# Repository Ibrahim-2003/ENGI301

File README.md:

# ENGI301
Engineering Design: Intro to Practical Electrical Engineering

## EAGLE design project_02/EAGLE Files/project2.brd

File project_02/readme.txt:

Github Link: https://github.com/Ibrahim-2003/ENGI301
--------------------------------------
Library Components:
POCKETBEAGLE (device and footprint)
POCKETBEAGLE_PWR (symbol)
POCKETBEAGLE_SIGNALS (symbol)
POCKETBEAGLE_MISC (symbol)
SPI_SCREEN (device, footprint, and symbol)
*** All other library components were imported from combo_lock.lbr ***
--------------------------------------
MicroFab Login:
USERNAME: isa1@rice.edu
PASSWORD: deeznuts
*** Note: Please excuse the silly password name, I had already created the account prior to knowing we were supposed to turn it in ***
--------------------------------------
Price Quotes:
*** Detailed in "MicroFab Price Quotes.csv" ***

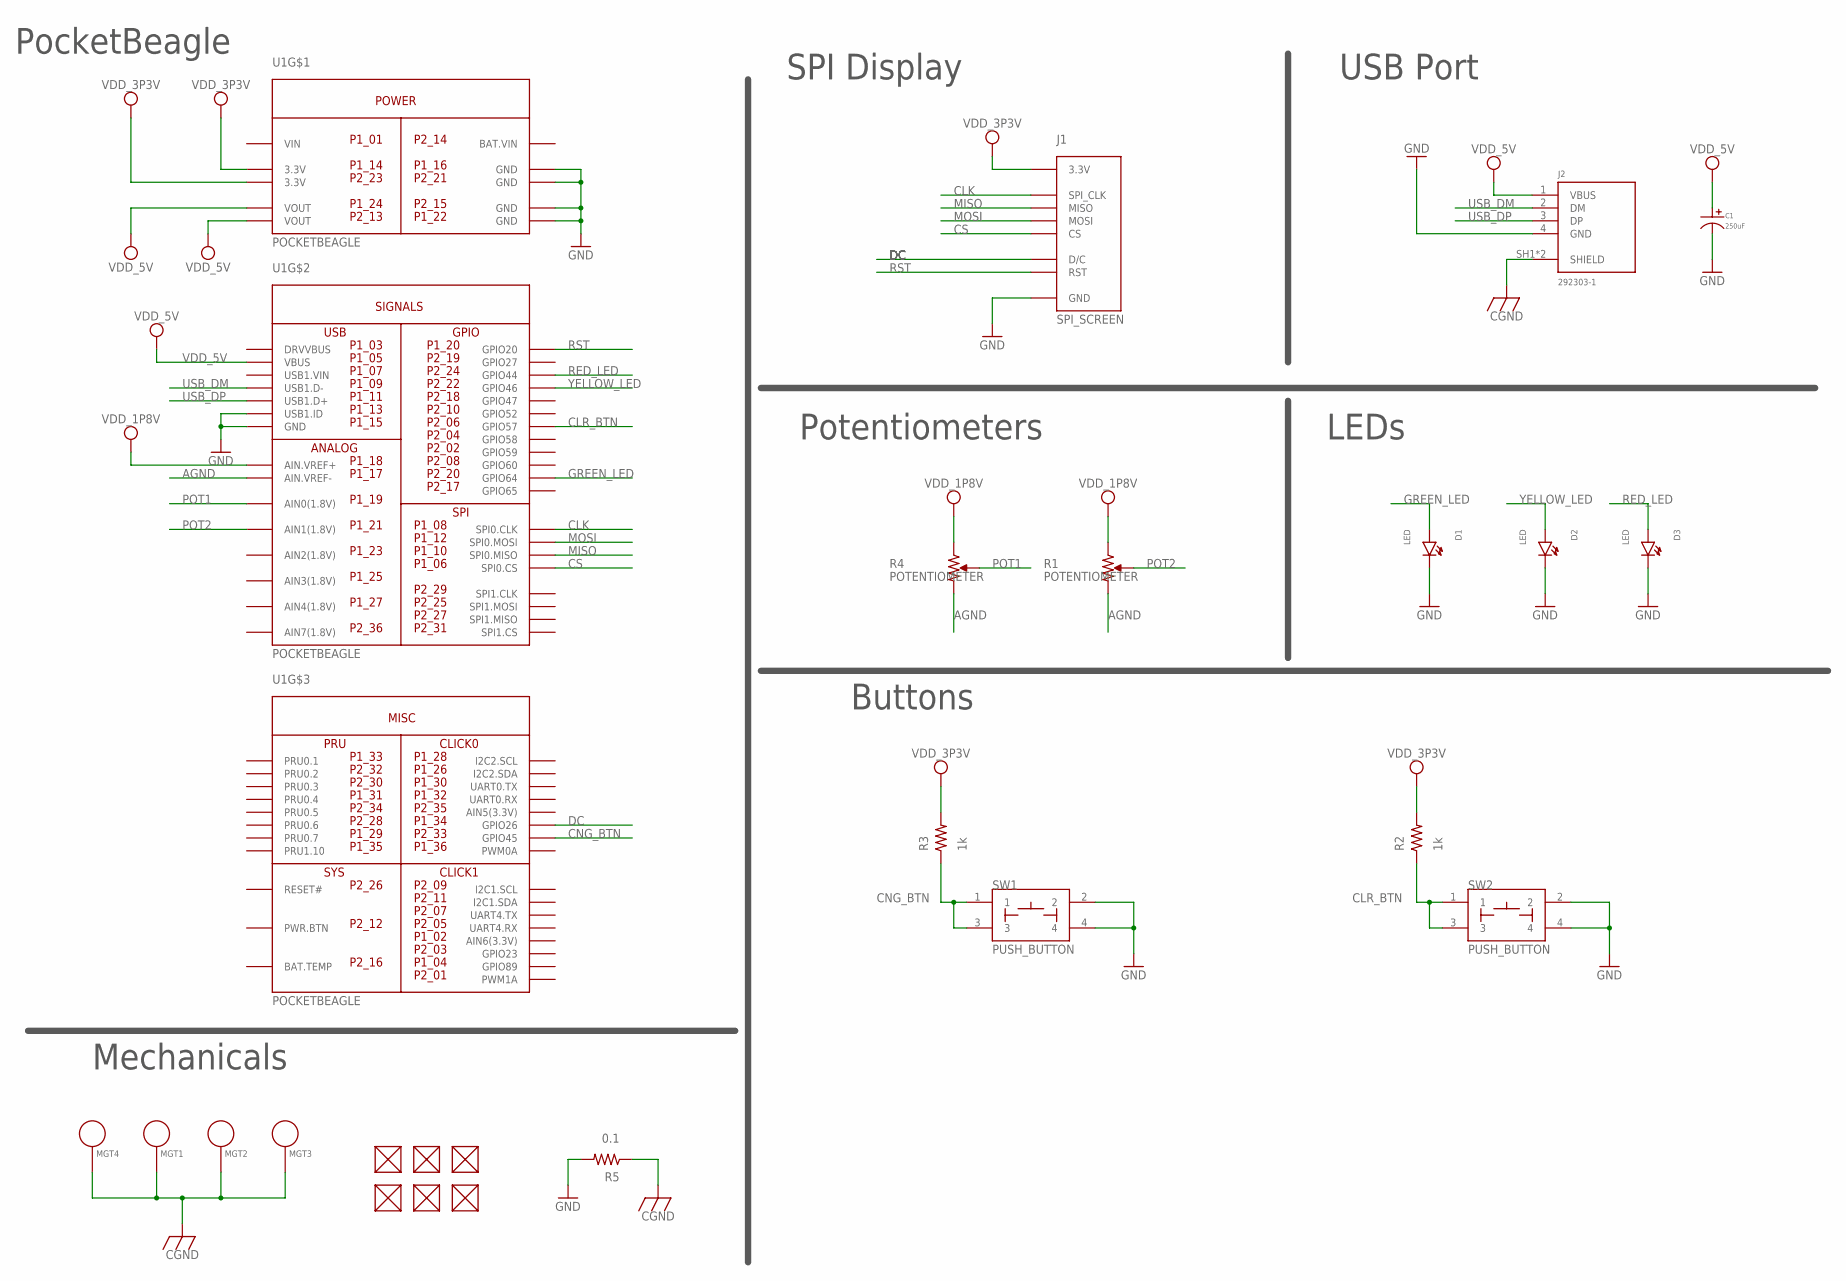
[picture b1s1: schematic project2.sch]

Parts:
C1: 250uF; CP10MM
D1, D2, D3: LED; EIA-STD
FUD1, FUD2, FUD3, FUD4, FUD5, FUD6: FIDUCIAL; FIDUCIAL_40MIL
J1: SPI_SCREEN
J2: 292303-1; TE_292303-1
MGT1, MGT2, MGT3, MGT4: MOUNTING_HOLE
R1, R4: POTENTIOMETER; POT-PO90S
R2, R3: 1k; R0603
R5: 0.1; R0603
SW1, SW2: PUSH_BUTTON; BUTTON_12.5MM
U1: POCKETBEAGLE

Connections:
AGND: R1.CW, R4.CW, U1.17@P1 (AIN.VREF-)
BAT.VIN: U1.14@P2 (BAT.VIN)
CGND: J2.SH1 (SHIELD), J2.SH2 (SHIELD), MGT1.P$1, MGT2.P$1, MGT3.P$1, MGT4.P$1, R5.1
CLK: J1.4@JP2 (SPI_CLK), U1.8@P1 (SPI0.CLK)
CLR_BTN: R2.1, SW2.1, SW2.3, U1.6@P2 (GPIO57)
CNG_BTN: R3.1, SW1.1, SW1.3, U1.33@P2 (GPIO45)
CS: J1.7@JP2 (CS), U1.6@P1 (SPI0.CS)
DC: J1.8@JP2 (D/C), U1.34@P1 (GPIO26)
GND: C1.P$2, D1.CATHODE, D2.CATHODE, D3.CATHODE, J1.1@JP2 (GND), J2.4 (GND), R5.2, SW1.2, SW1.4, SW2.2, SW2.4, U1.13@P1 (USB1.ID), U1.15@P1 (GND), U1.15@P2 (GND), U1.16@P1 (GND), U1.21@P2 (GND), U1.22@P1 (GND)
GREEN_LED: D1.ANODE, U1.20@P2 (GPIO64)
MISO: J1.5@JP2 (MISO), U1.10@P1 (SPI0.MISO)
MOSI: J1.6@JP2 (MOSI), U1.12@P1 (SPI0.MOSI)
POT1: R4.S, U1.19@P1 (AIN0(1.8V))
POT2: R1.S, U1.21@P1 (AIN1(1.8V))
RED_LED: D3.ANODE, U1.24@P2 (GPIO44)
RST: J1.9@JP2 (RST), U1.20@P1 (GPIO20)
USB_DM: J2.2 (DM), U1.9@P1 (USB1.D-)
USB_DP: J2.3 (DP), U1.11@P1 (USB1.D+)
VDD_1P8V: R1.CCW, R4.CCW, U1.18@P1 (AIN.VREF+)
VDD_3P3V: J1.3@JP2 (3.3V), R2.2, R3.2, U1.14@P1 (3.3V), U1.23@P2 (3.3V)
VDD_5V: C1.P$1, J2.1 (VBUS), U1.5@P1 (VBUS), U1.13@P2 (VOUT), U1.24@P1 (VOUT)
VIN: U1.1@P1 (VIN)
YELLOW_LED: D2.ANODE, U1.22@P2 (GPIO46)

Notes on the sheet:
PocketBeagle
SPI Display
USB Port
Potentiometers
LEDs
Buttons
Mechanicals

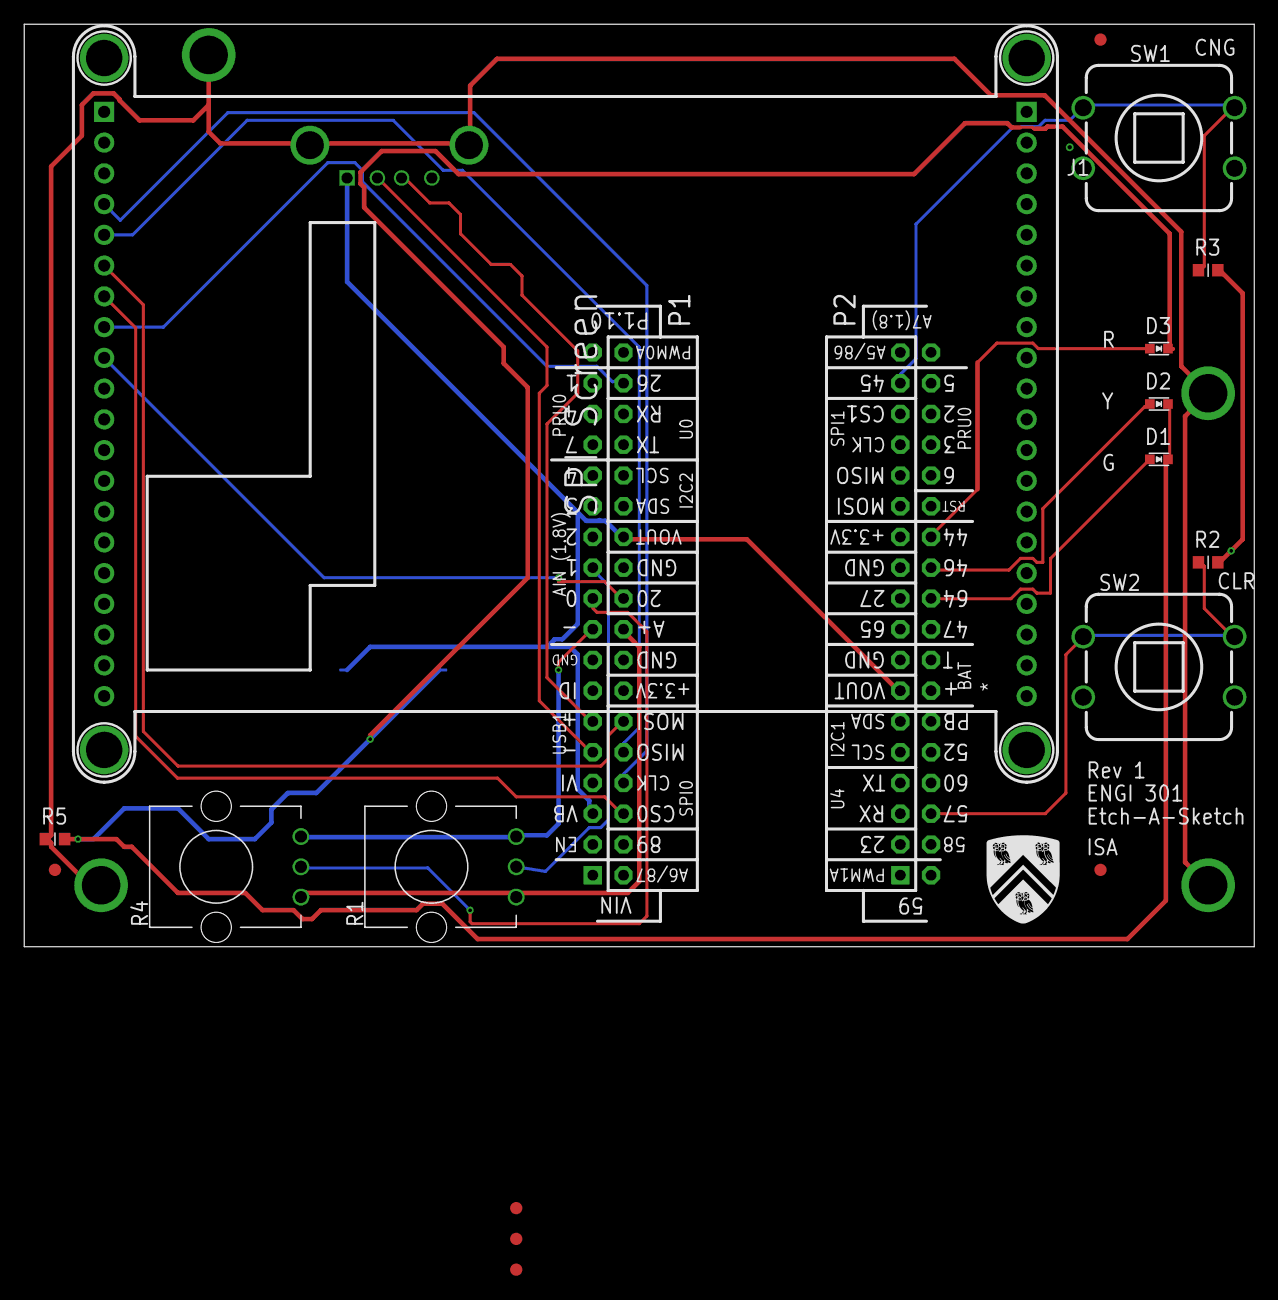
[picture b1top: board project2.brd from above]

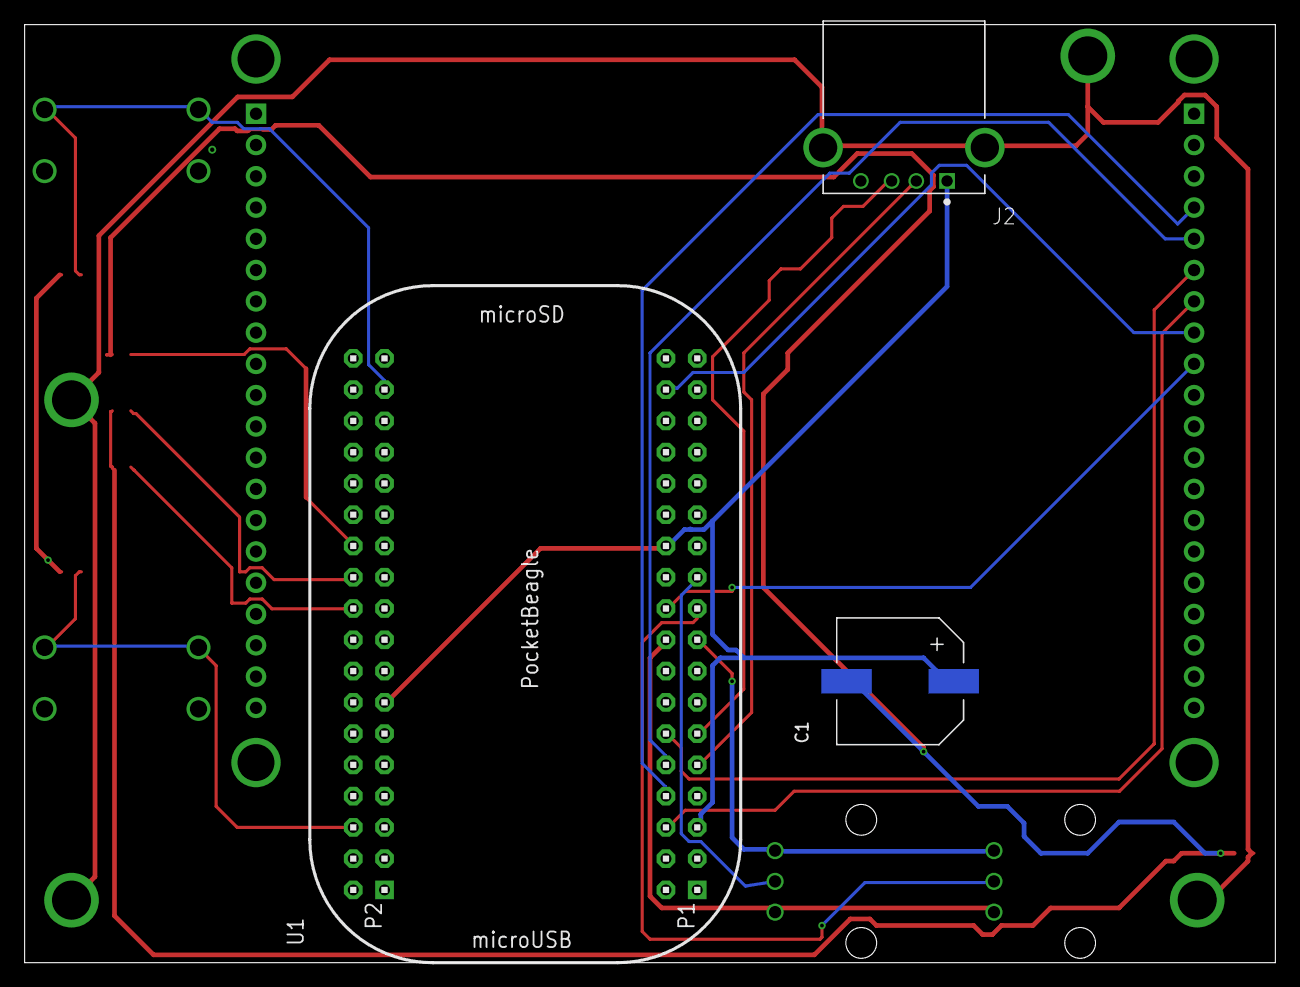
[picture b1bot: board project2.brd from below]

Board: 4 copper layers, 101.6 x 76.2 mm, 24 parts (3 on the bottom side), 21 nets.

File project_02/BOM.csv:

Designator,Value,Footprint,Populate,MPN,Manufacturer
C1,250uF,CP10MM,1,MF-CAP-10MM-220uF,MacroFab
D1,LED,EIA-STD,1,MF-LED-0603-GREEN,MacroFab
D2,LED,EIA-STD,1,MF-LED-0603-GREEN,MacroFab
D3,LED,EIA-STD,1,MF-LED-0603-GREEN,MacroFab
FUD1,FIDUCIAL,FIDUCIAL_40MIL,0,5-1567064-5,TE Connectivity / AMP
FUD2,FIDUCIAL,FIDUCIAL_40MIL,0,5-1567064-5,TE Connectivity / AMP
FUD3,FIDUCIAL,FIDUCIAL_40MIL,0,5-1567064-5,TE Connectivity / AMP
FUD4,FIDUCIAL,FIDUCIAL_40MIL,0,5-1567064-5,TE Connectivity / AMP
FUD5,FIDUCIAL,FIDUCIAL_40MIL,0,5-1567064-5,TE Connectivity / AMP
FUD6,FIDUCIAL,FIDUCIAL_40MIL,0,5-1567064-5,TE Connectivity / AMP
J1,SPI_SCREEN,SPI_SCREEN,1,1770,Adafruit Industries
J2,292303-1,TE_292303-1,1,292303-1,TE Connectivity
MGT1,MOUNTING_HOLE,MOUNTING_HOLE,0,2516672_WO_CORNER_MOUNTING_HOLES,Texas Instruments
MGT2,MOUNTING_HOLE,MOUNTING_HOLE,0,2516672_WO_CORNER_MOUNTING_HOLES,Texas Instruments
MGT3,MOUNTING_HOLE,MOUNTING_HOLE,0,2516672_WO_CORNER_MOUNTING_HOLES,Texas Instruments
MGT4,MOUNTING_HOLE,MOUNTING_HOLE,0,2516672_WO_CORNER_MOUNTING_HOLES,Texas Instruments
R1,POTENTIOMETER,POT-PO90S,1,MF-RES-TC33X-10K,MacroFab
R2,1k,R0603,1,MF-RES-0603-1K,MacroFab
R3,1k,R0603,1,MF-RES-0603-1K,MacroFab
R4,POTENTIOMETER,POT-PO90S,1,MF-RES-TC33X-10K,MacroFab
R5,0.1,R0603,1,ERJ-L03KF10CV,Panasonic
SW1,PUSH_BUTTON,BUTTON_12.5MM,1,TINKERKIT PUSHBUTTON,Arduino
SW2,PUSH_BUTTON,BUTTON_12.5MM,1,TINKERKIT PUSHBUTTON,Arduino
U1,POCKETBEAGLE,POCKETBEAGLE,1,POCKETBEAGLE,BeagleBoard

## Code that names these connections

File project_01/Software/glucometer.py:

# -*- coding: utf-8 -*-
"""
--------------------------------------------------------------------------
Glucometer Code
--------------------------------------------------------------------------
License:   
Copyright 2022 Ibrahim Al-Akash

Redistribution and use in source and binary forms, with or without 
modification, are permitted provided that the following conditions are met:

1. Redistributions of source code must retain the above copyright notice, this 
list of conditions and the following disclaimer.

2. Redistributions in binary form must reproduce the above copyright notice, 
this list of conditions and the following disclaimer in the documentation 
and/or other materials provided with the distribution.

3. Neither the name of the copyright holder nor the names of its contributors 
may be used to endorse or promote products derived from this software without 
specific prior written permission.

THIS SOFTWARE IS PROVIDED BY THE COPYRIGHT HOLDERS AND CONTRIBUTORS "AS IS" 
AND ANY EXPRESS OR IMPLIED WARRANTIES, INCLUDING, BUT NOT LIMITED TO, THE 
IMPLIED WARRANTIES OF MERCHANTABILITY AND FITNESS FOR A PARTICULAR PURPOSE ARE 
DISCLAIMED. IN NO EVENT SHALL THE COPYRIGHT HOLDER OR CONTRIBUTORS BE LIABLE 
FOR ANY DIRECT, INDIRECT, INCIDENTAL, SPECIAL, EXEMPLARY, OR CONSEQUENTIAL 
DAMAGES (INCLUDING, BUT NOT LIMITED TO, PROCUREMENT OF SUBSTITUTE GOODS OR 
SERVICES; LOSS OF USE, DATA, OR PROFITS; OR BUSINESS INTERRUPTION) HOWEVER 
CAUSED AND ON ANY THEORY OF LIABILITY, WHETHER IN CONTRACT, STRICT LIABILITY, 
OR TORT (INCLUDING NEGLIGENCE OR OTHERWISE) ARISING IN ANY WAY OUT OF THE USE 
OF THIS SOFTWARE, EVEN IF ADVISED OF THE POSSIBILITY OF SUCH DAMAGE.
--------------------------------------------------------------------------

Use the following hardware components to make a noninvasive NIR-based glucometer:
    - HT16K33 Display
    - Button
    - Red LED
    - Yellow LED
    - Green LED
    - White Indicator LEDs (x2)

Requirements:
    - Hardware:
        - Button
            - Waiting for button press to initiate sensor function
            - Upon completion of glucose measurement, wait for button input
            - Record press time and return
        - Display shows the status of the glucometer and glucose concentration after measurement

    - User Interaction (UI):
        - Needs to be able to initiate glucose reading
            - Can change the units of the glucose concentration displayed from mg/dL to mmol/L if button is pressed
            - Clear the measurement if the button is held for a certain interval
        - Easily interpret the glucose reading as healthy, moderate dysglycemia, or severe dysglycemia

Uses:
    - HT16K33 display library developed in class
        
"""

# ------------------------------------------------------------------------
# Constants
# ------------------------------------------------------------------------

# None

# ------------------------------------------------------------------------
# Global variables
# ------------------------------------------------------------------------

# None

# ------------------------------------------------------------------------
# Functions / Classes
# ------------------------------------------------------------------------

import Adafruit_BBIO.GPIO as GPIO
import Adafruit_BBIO.ADC as ADC

import ht16k33 as HT16K33
from AS726X import IR_SENSOR

class Sensor():
    """ Sensor """
    clear_time = None
    red_led = None
    yellow_led = None
    green_led = None
    mmol_led = None
    mgdl_led = None
    display = None
    button = None
    ir_sensor = None
    sensor_reading = None

    def __init__(self, clear_time=3.0, button="P2_2",
                red_led="P2_6", yellow_led="P2_4",
                green_led="P2_8", mmol_led="P2_10",
                mgdl_led="P1_6", ir_sensor=0x49,
                ir_bus=2, display_address=0x70,
                display_bus=1):
        """ Initialize variables and set up display """
        self.clear_time = clear_time
        self.button = button
        self.red_led = red_led
        self.yellow_led = yellow_led
        self.green_led = green_led
        self.mmol_led = mmol_led
        self.mgdl_led = mgdl_led
        self.ir_sensor = IR_SENSOR(ir_bus, ir_sensor)
        self.display = HT16K33.HT16K33(display_bus, display_address)

        self._setup()

    # End def

    def _setup(self):
        """ Setup the hardware components """

        # Initialize Display
        self.set_display_dash()

        # Initialize Button
        GPIO.setup(self.button, GPIO.IN)

        # Initialize LEDs
        GPIO.setup(self.red_led, GPIO.OUT)
        GPIO.setup(self.yellow_led, GPIO.OUT)
        GPIO.setup(self.green_led, GPIO.OUT)
        GPIO.setup(self.mmol_led, GPIO.OUT)
        GPIO.setup(self.mgdl_led, GPIO.OUT)

        # IR Sensor is initialized when object is created

    # End def

    def set_display_dash(self):
        """Set display to word "----" """
        self.display.text("----")

    # End def

    def glucose_concentration(self):
        """Calculate glucose concentration from sensor NIR spectroscopy measurement"""
        pass

    # End def

    def read_sensor(self):
        """Read sensor value and save to object"""
        value = self.ir_sensor.take_measurements()
        self.sensor_reading = value

    # End def

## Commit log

2022-09-11 Updating README.md
2022-09-19 assignment 03 submission
2022-09-25 Assignment 4 V1
2022-09-26 Assignment 4 V2
2022-09-28 Project Proposal Submission
2022-12-14 Project 2
    Version 1.0
2022-12-14 Project 2
    Updated Link in readme.txt
2022-12-14 Project 2
    Added project description and converted readme.txt to readme.md
2022-12-14 Project 2
    Fixed formatting of readme.md file
2022-12-14 Project 2
    Restructured file directories to match project guidelines and replaced the EAGLE BOM with the MacroFab BOM
2022-12-14 Project 1
    Version 1
2022-12-14 Projects 1 and 2 Submission
    Fixed readme's and included EAGLE files with the correct board with logo
